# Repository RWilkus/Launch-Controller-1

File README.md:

# Launch-Controller-1
Model Rocket Launch Controller

Designer: Ryan Wilkus

Audience: Cub Scouts/Scouts BSA

(Rev A Image)

Ordering:

PCB - [PCBWay.com](https://www.pcbway.com/QuickOrderOnline.aspx)
 - Upload Gerbers
 - 2 layer, 1.6mm thickness, FR-4 material, 1oz Cu, Black soldermask, White silkscreen, HASL with Lead surface finish
 - Adjust board quantity to find maximum boards per price. 10 boards was the same price as 1.

Parts - [Digikey.com](https://www.digikey.com/ordering/shoppingcart?lang=en)
 - Upload LaunchController1 BOM.xlsx to purchase

3D printing:

Resolution: 0.2mm, Infill: 20%, Filiment: 1.75mm Supports: Yes, Rafts: Yes, 

PCB Assembly Instructions:

Assemble and solder in order

R1-R6: Bidirectional so orientation doesn't matter. 

     (R1,R4,R5) 300 Ohm: Orange, Black, Brown, Gold
     
     (R2,R3,R6) 4.7k Ohm: Yellow, Purple, Red, Gold
     
D1/D2: Bidirectional so orientation doesn't matter

PTC1: Bidirectional so orientation doesn't matter

LED1/LED2: LED1= Red, LED2=Green. Long lead goes into the positive symbol(+)

Q1/Q2: Bend outside leads to match hole spacing. Verify larger flat side matches flat silkscreen. 

J1: Orient connector to edge of board

SW1: Orientation doesn't matter. 

SW2: Make sure SW2 flat side matches silkscreen

BT1: Use double sided tape or super glue to secure to board. Solder leads from the top side.

Cutoff excess component leads

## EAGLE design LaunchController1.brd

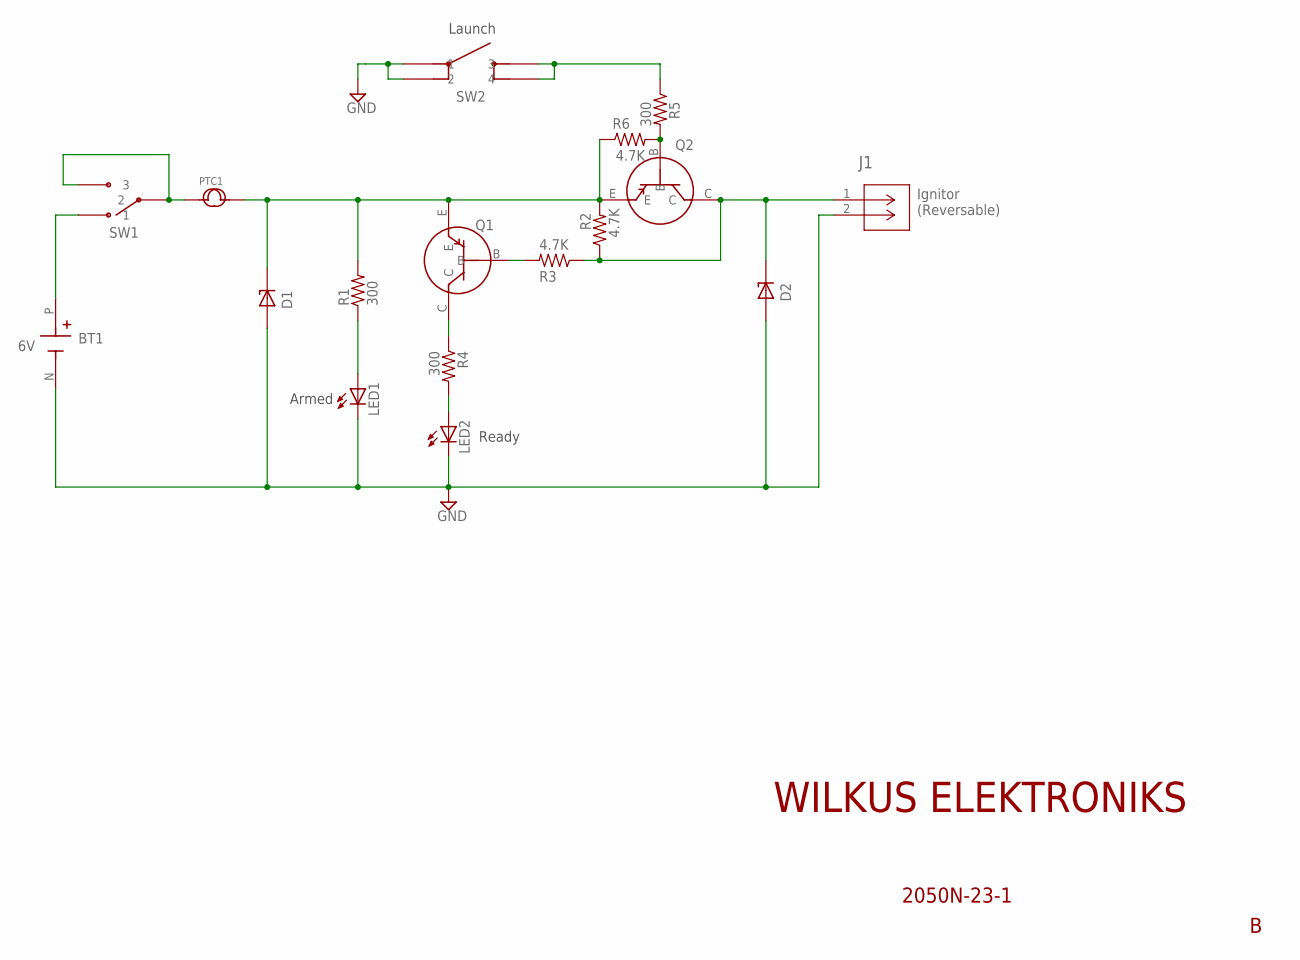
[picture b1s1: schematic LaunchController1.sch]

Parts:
BT1: 6V; BAT_2477
D1, D2: P6KE75CA; DIOAD1300W80L670D310
J1: 691137710002; CONN2_710002_WRE
LED1, LED2: LED5MM
PTC1: 0ZRG0120FF2E; 0ZRG
Q1, Q2: BJT_PNP; TO92-
R1, R4, R5: 300; 0309/12
R2, R3, R6: 4.7K; 0309/12
SW1: ANT11SF1CQE
SW2: D6R40F2LFS

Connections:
GND: BT1.N (NEG), D1.A, D2.A, J1.2, LED1.K (C), LED2.K (C), SW2.P$1 (1), SW2.P$2 (2)
IGNTR_HOT: D2.C, J1.1, Q2.C, R2.1, R3.1
unnamed: Q1.B, R3.2
unnamed: PTC1.1, SW1.P$2 (2), SW1.P$3 (3)
unnamed: Q2.B, R5.2, R6.2
unnamed: LED1.A, R1.1
unnamed: R5.1, SW2.P$3 (3), SW2.P$4 (4)
unnamed: D1.C, PTC1.2, Q1.E, Q2.E, R1.2, R2.2, R6.1
unnamed: LED2.A, R4.2
unnamed: Q1.C, R4.1
PWR: BT1.P (POS), SW1.P$1 (1)

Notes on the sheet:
Ready
Armed
Launch
Ignitor (Reversable)

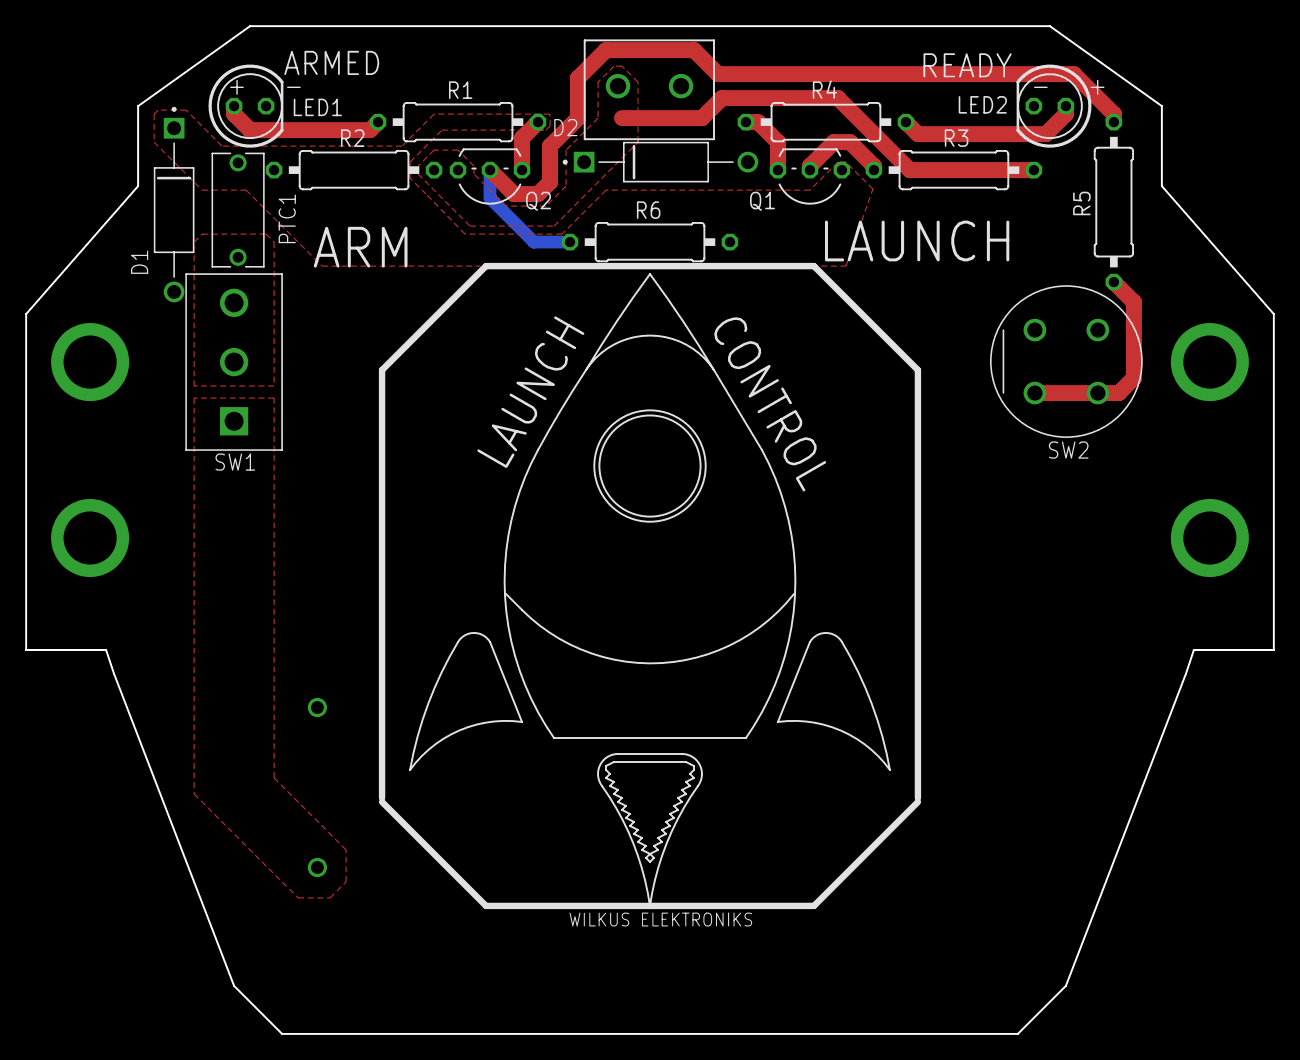
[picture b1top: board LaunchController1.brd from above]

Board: 2 copper layers, 99.1 x 80.0 mm, 17 parts (1 on the bottom side), 11 nets.

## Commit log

2023-06-15 Add files via upload
    Rev B commit - Working prototype
2023-06-15 Add files via upload
    Rev B BOM commit
2023-06-15 Add files via upload
    3D print files
2023-06-15 Image File Rev A

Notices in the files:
parts and their libraries:
COPYRIGHT: Copyright (C) 2023 Ultra Librarian. All rights reserved.
